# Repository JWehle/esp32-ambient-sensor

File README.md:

# esp32-ambient-sensor
ESP32-based room temperature, humidity, light level, and motion monitor.

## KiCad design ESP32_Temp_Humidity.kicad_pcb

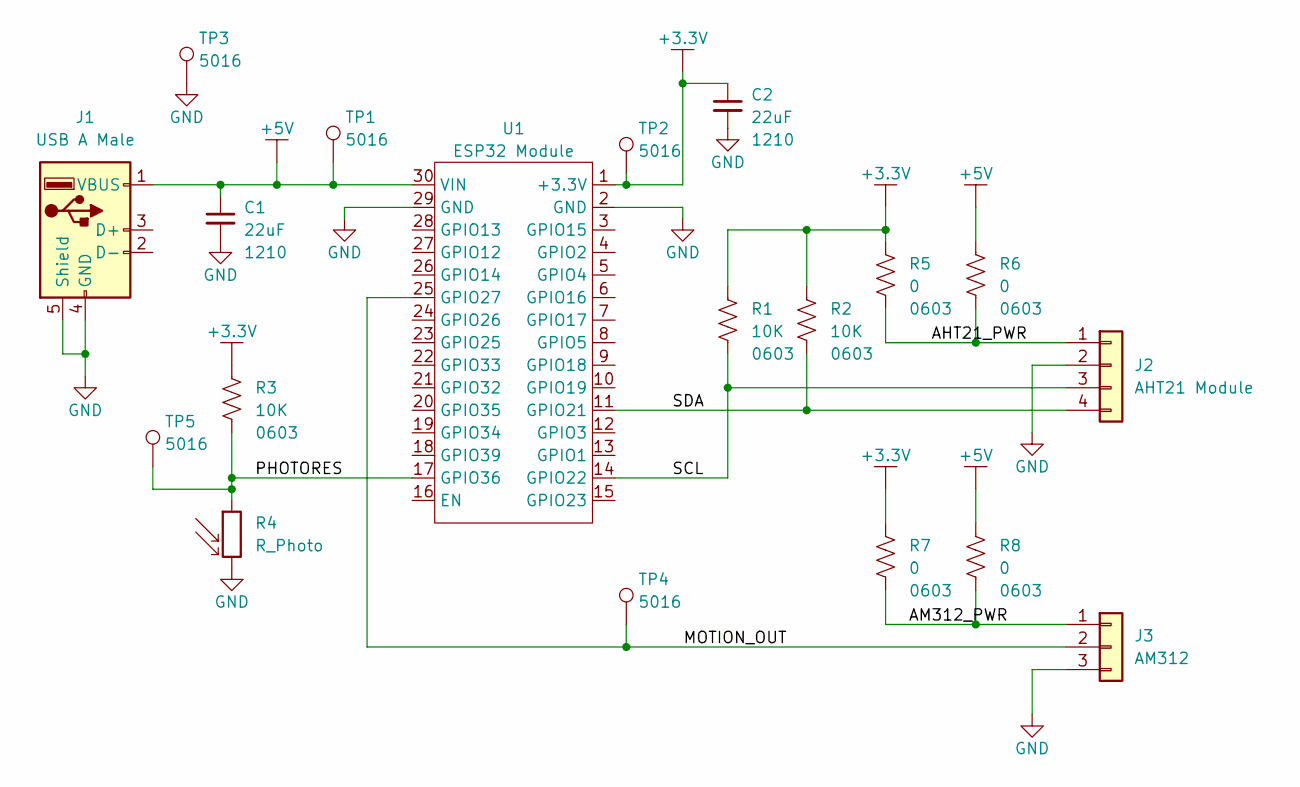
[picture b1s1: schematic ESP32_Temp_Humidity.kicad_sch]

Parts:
C1, C2: 22uF; C_1210_3225Metric_Pad1.33x2.70mm_HandSolder
J1: USB A Male; USB_A_CNCTech_1001-011-01101_Horizontal
J2: AHT21 Module; PinSocket_1x04_P2.54mm_Vertical
J3: AM312; PinSocket_1x03_P2.54mm_Vertical
R1, R2, R3: 10K; R_0603_1608Metric_Pad0.98x0.95mm_HandSolder
R4: R_Photo; LED_D5.0mm
R5, R6, R7, R8: 0; R_0603_1608Metric_Pad0.98x0.95mm_HandSolder
TP1, TP2, TP3, TP4, TP5: 5016; TestPoint_Keystone_5016_Compact
U1: ESP32 Module; ESP32_MODULE

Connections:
+3.3V: C2.1, R1.1, R2.1, R3.1, R5.1, R7.1, TP2.1, U1.1 (+3.3V)
+5V: C1.1, J1.1 (VBUS), R6.1, R8.1, TP1.1, U1.30 (VIN)
/AHT21_PWR: J2.1, R5.2, R6.2
/AM312_PWR: J3.1, R7.2, R8.2
/MOTION_OUT: J3.2, TP4.1, U1.25 (GPIO27)
/PHOTORES: R3.2, R4.1, TP5.1, U1.17 (GPIO36)
/SCL: J2.3, R1.2, U1.14 (GPIO22)
/SDA: J2.4, R2.2, U1.11 (GPIO21)
GND: C1.2, C2.2, J1.4 (GND), J1.5 (Shield), J2.2, J3.3, R4.2, TP3.1, U1.2 (GND), U1.29 (GND)

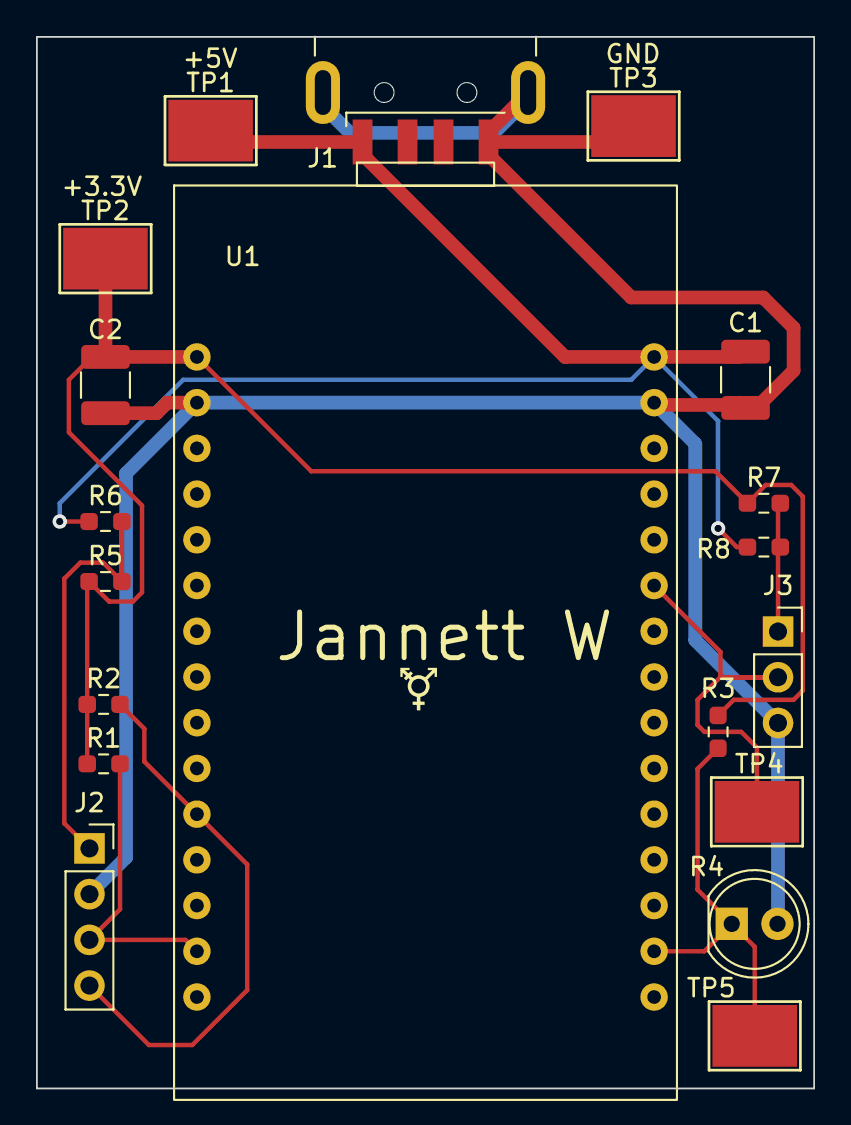
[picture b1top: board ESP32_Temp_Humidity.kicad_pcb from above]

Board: 2 copper layers, 43.2 x 58.4 mm, 19 parts (0 on the bottom side), 9 nets.
